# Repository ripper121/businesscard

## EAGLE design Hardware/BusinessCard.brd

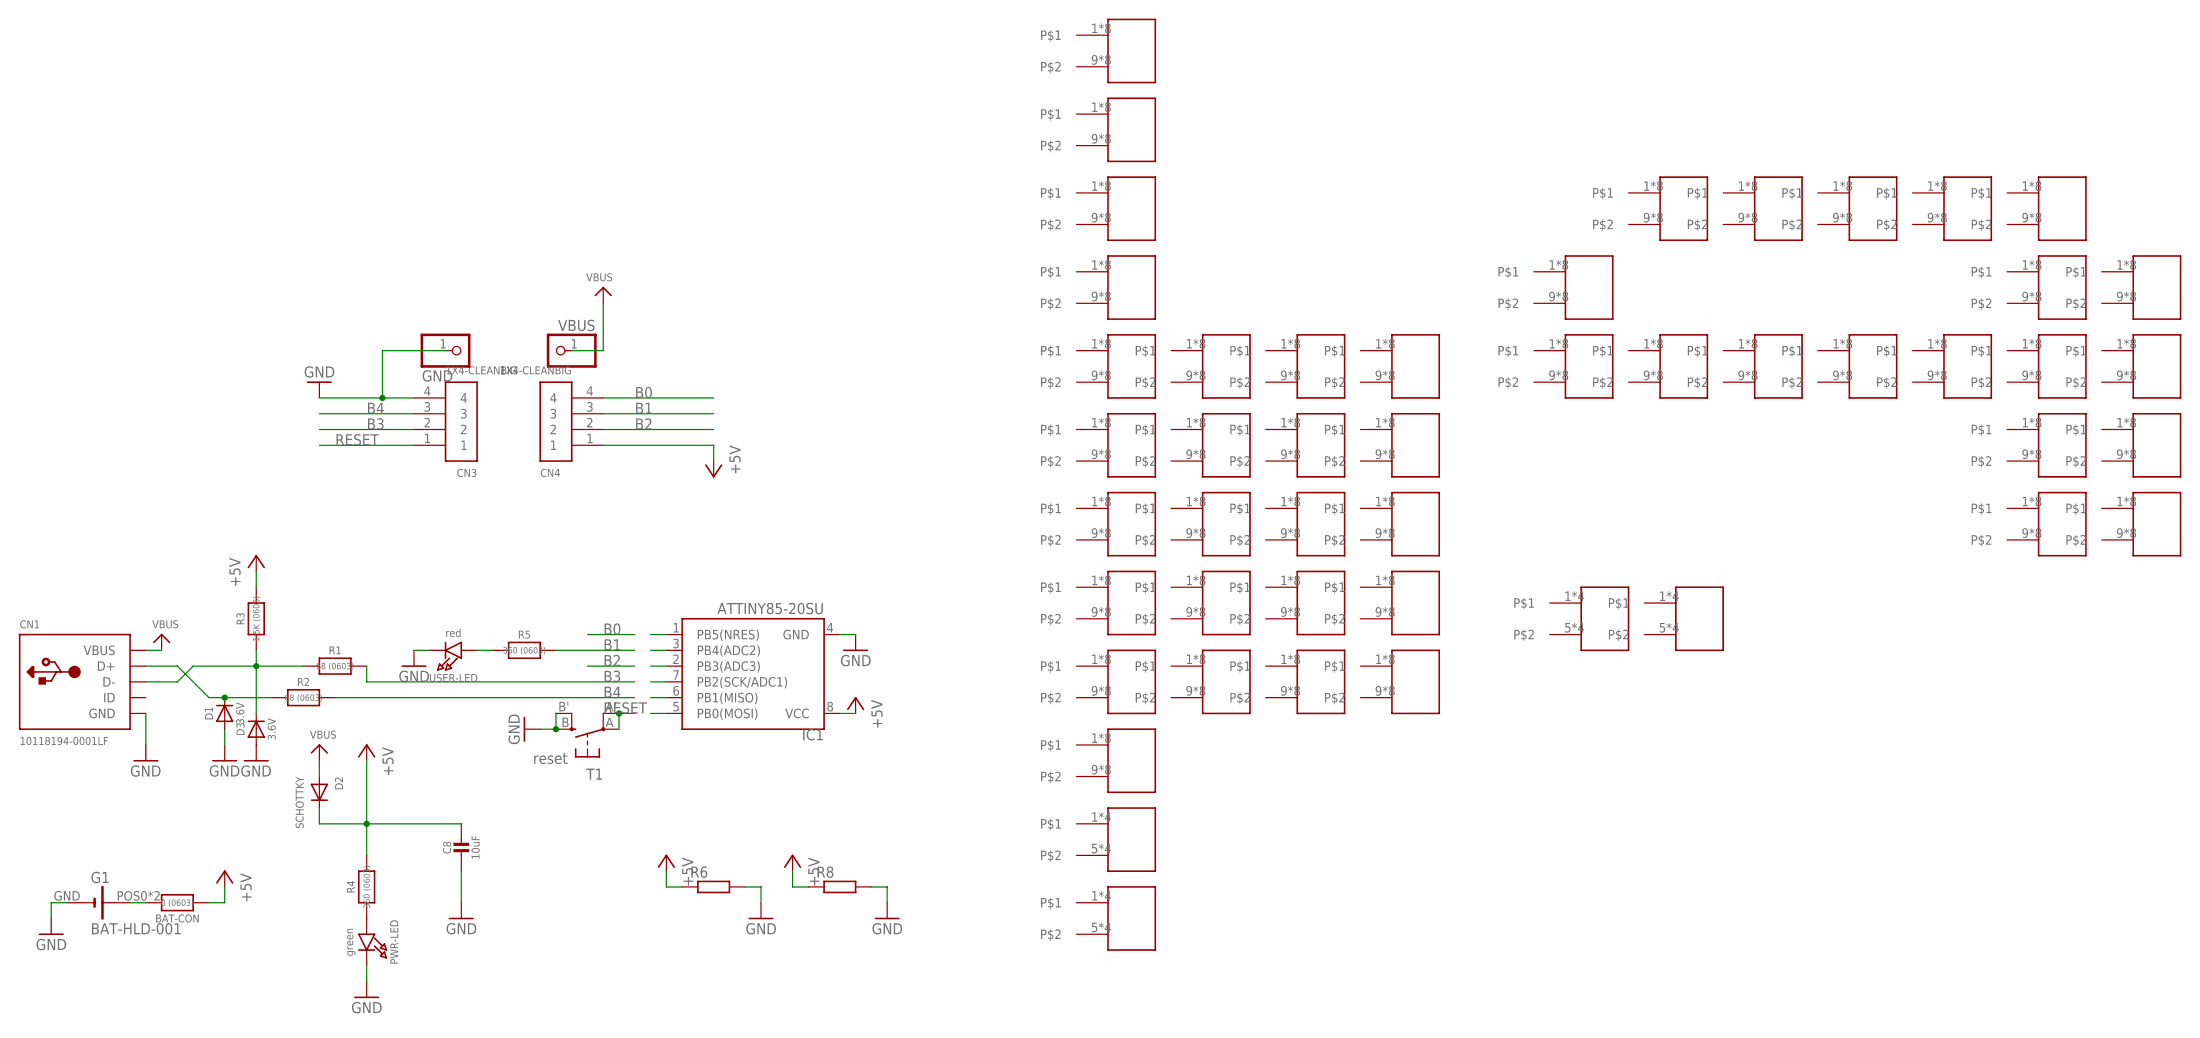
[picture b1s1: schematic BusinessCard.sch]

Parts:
BAT-CON: 0 (0603); 0603-NO
C8: 10uF; 0805-NO
CN1: 10118194-0001LF; 4UCONN_20329
CN3, CN4: 1X4-CLEANBIG; 1X04-CLEANBIG
D1, D3: 3.6V; SOD-323
D2: SCHOTTKY; SOD-123FL
G1: BAT-HLD-001; BK-889
GND: PINHD-1X1CB; 1X01-CLEANBIG
IC1: ATTINY85-20SU; SO08-EIAJ
PWR-LED: green; CHIPLED_0805_NOOUTLINE
R1, R2: 68 (0603); 0603-NO
R3: 1.5K (0603); 0603-NO
R4, R5: 360 (0603); 0603-NO
R6, R8: R-EU_M0805; M0805
T1: reset; EVQ-Q2
U$5, U$6, U$7, U$8, U$9, U$13, U$15, U$17, U$18, U$19, U$20, U$21, U$22, U$23, U$24, U$25, U$26, U$27, U$28, U$29, U$30, U$31, U$32, U$33, U$34, U$35, U$36, U$37, U$40, U$43, U$45, U$48, U$50, U$53, U$55, U$56, U$57, U$58, U$59, U$60, U$61, U$62, U$63, U$64: SMD0805; SMD-0603
U$38, U$39, U$65, U$66: SMD-4
USER-LED: red; CHIPLED_0805_NOOUTLINE
VBUS: PINHD-1X1CB; 1X01-CLEANBIG

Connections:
+5V: BAT-CON.1, C8.1, CN4.1, D2.C, IC1.8 (VCC), R3.2, R4.2, R6.1, R8.1
B0: CN4.4, IC1.5 (PB0(MOSI))
B1: CN4.3, IC1.6 (PB1(MISO)), R5.2
B2: CN4.2, IC1.7 (PB2(SCK/ADC1))
B3: CN3.2, IC1.2 (PB3(ADC3)), R1.2
B4: CN3.3, IC1.3 (PB4(ADC2)), R2.2
GND: C8.2, CN1.BASE@1 (GND), CN1.BASE@2 (GND), CN1.GND, CN1.SPRT@1 (GND), CN1.SPRT@2 (GND), CN1.SPRT@3 (GND), CN1.SPRT@4 (GND), CN3.4, D1.A, D3.A, G1.GND (-), GND.1, IC1.4 (GND), PWR-LED.C, R6.2, R8.2, T1.B (S), T1.B' (S1), USER-LED.C
unnamed: R5.1, USER-LED.A
unnamed: CN1.D+, D1.C, R2.1
unnamed: BAT-CON.2, G1.POS0 (+), G1.POS1 (+)
unnamed: CN1.D-, D3.C, R1.1, R3.1
unnamed: PWR-LED.A, R4.1
RESET: CN3.1, IC1.1 (PB5(NRES)), T1.A, T1.A' (P1)
VBUS: CN1.VBUS, D2.A, VBUS.1

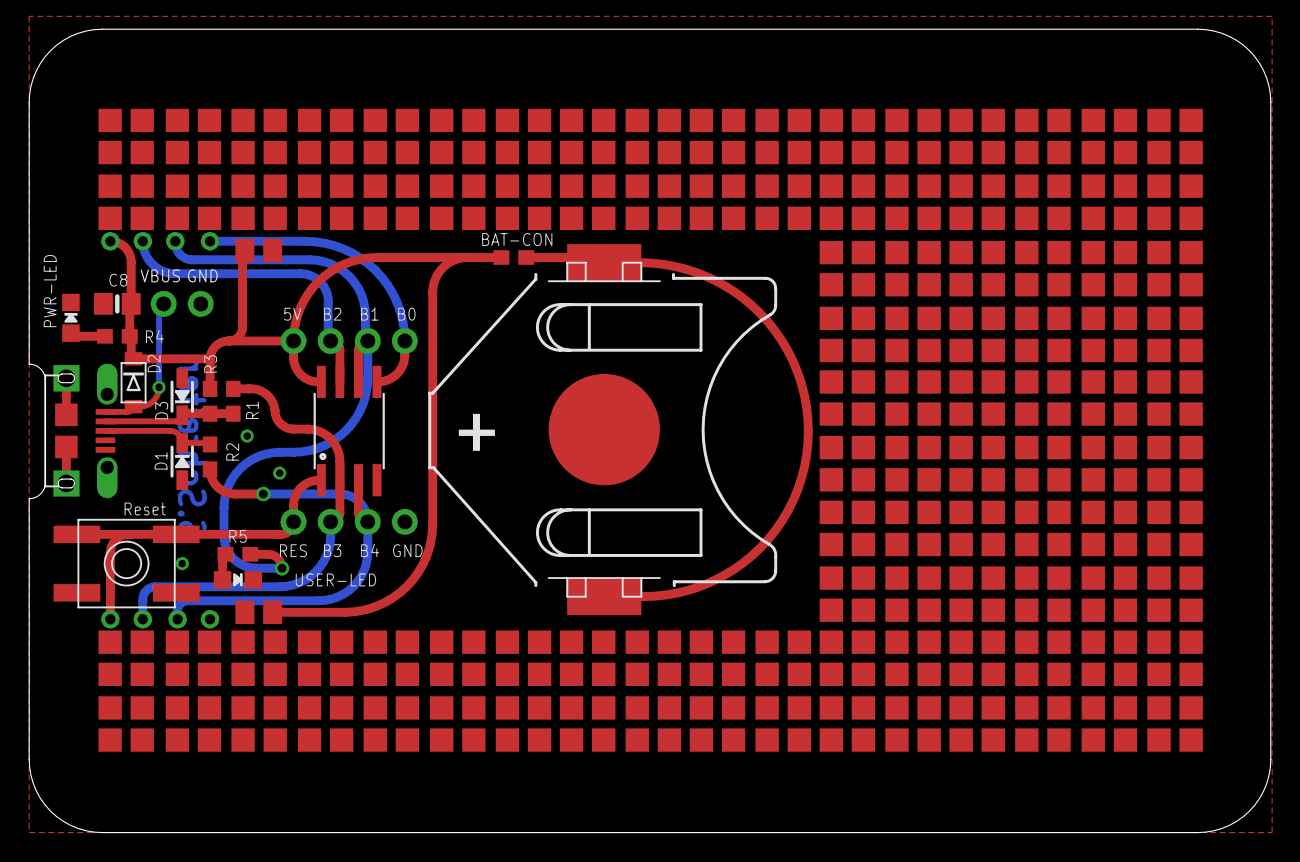
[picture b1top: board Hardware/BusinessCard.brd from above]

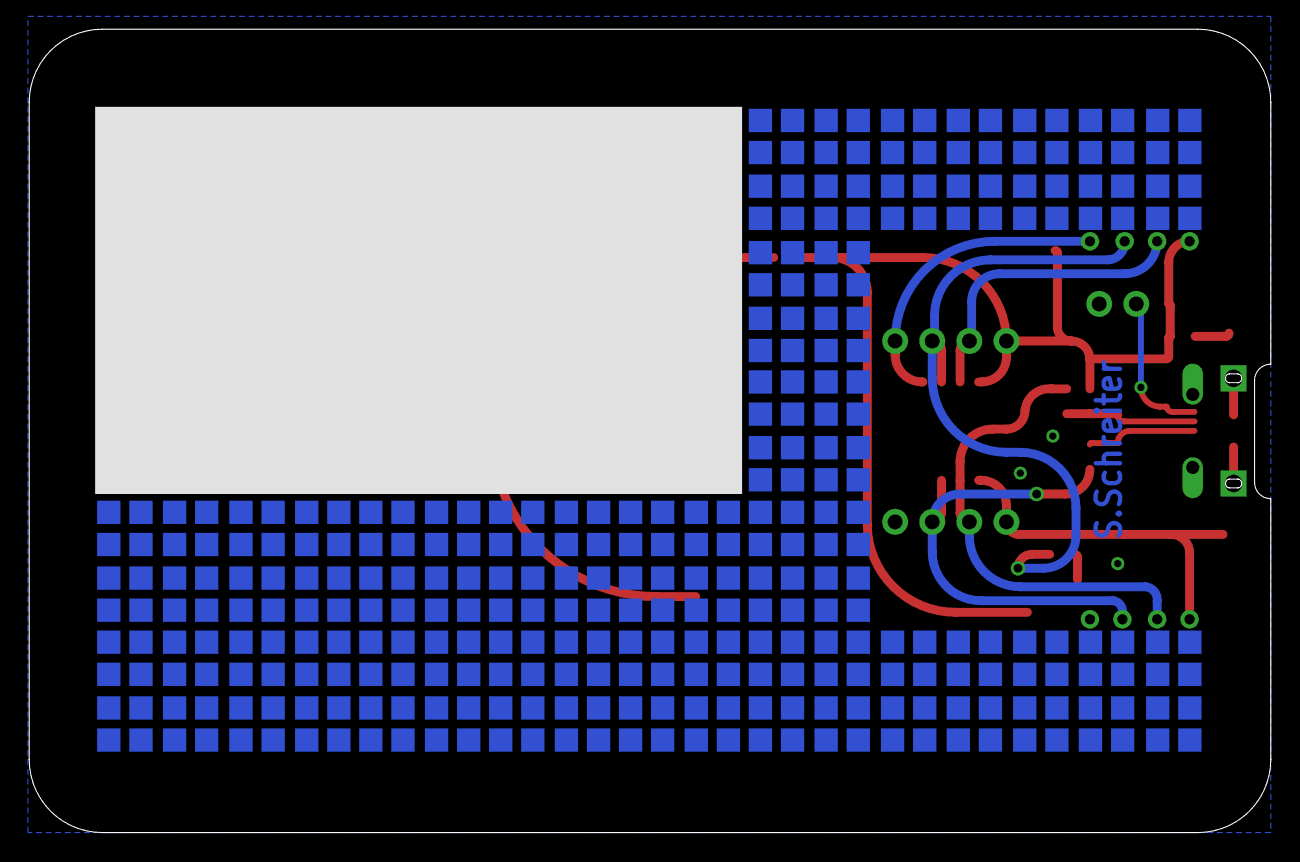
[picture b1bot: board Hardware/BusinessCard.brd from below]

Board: 2 copper layers, 85.0 x 55.0 mm, 70 parts (21 on the bottom side), 14 nets.

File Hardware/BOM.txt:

Stückliste exportiert aus C:/Users/sts/Documents/eagle/BusinessCard/BusinessCard.sch am 04.05.2016 13:13

Qty Value           Device                    Package                Parts                                                                                                                                                                                                                                                             Description                                PROD_ID  VALUE                                                                                                                                                                                                                                                                 RESISTOR, European symbol                                        
1   Tiny85-20-SMT   ATTINY45TINY85-20-SMT     SO08-EIAJ              IC1                                     
1   10118194-0001LF USBMICRO_20329            4UCONN_20329           CN1                                                   
1   BAT-HLD-001     BK-889                    BK-889                 G1
1   SCHOTTKY        DIODE_SOD-123FL           SOD-123FL              D2
2   68 (0603)       RESISTOR_0603_NOOUT       0603-NO                R1, R2
1   green           LED0805_NOOUTLINE         CHIPLED_0805_NOOUTLINE PWR-LED                                                              
1   red             LED0805_NOOUTLINE         CHIPLED_0805_NOOUTLINE USER-LED
2   360 (0603)      RESISTOR_0603_NOOUT       0603-NO                R4, R5
1   1.5K (0603)     RESISTOR_0603_NOOUT       0603-NO                R3
1   0 (0603)        RESISTOR_0603_NOOUT       0603-NO                BAT-CON    
1   10uF            CAP_CERAMIC0805-NOOUTLINE 0805-NO                C8
2   3.6V            DIODESOD-323              SOD-323                D1, D3

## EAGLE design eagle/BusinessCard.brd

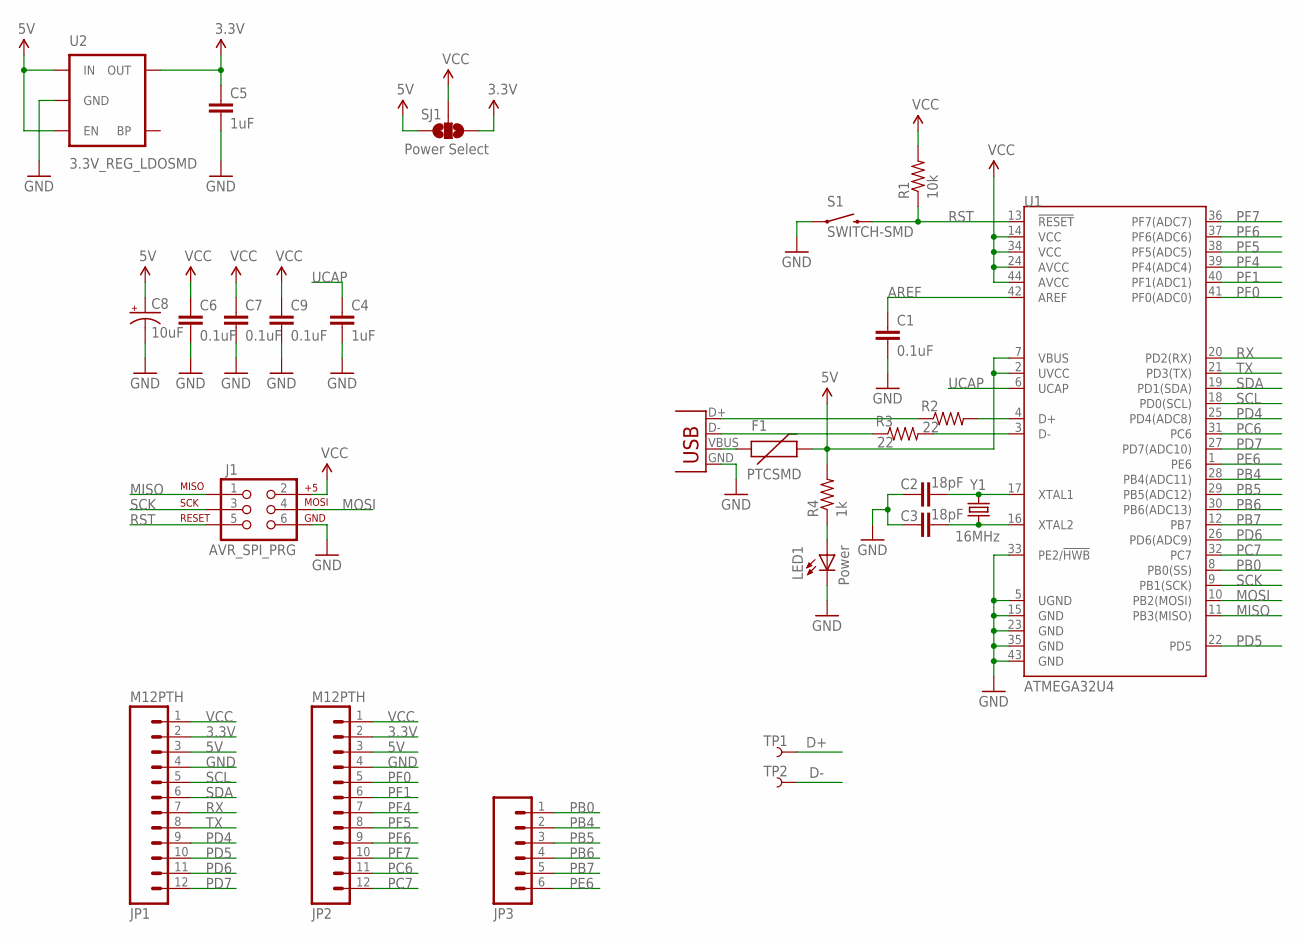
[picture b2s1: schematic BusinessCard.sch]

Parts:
C1, C6, C7, C9: 0.1uF; 0402-CAP
C2, C3: 18pF; 0402-CAP
C4, C5: 1uF; 0402-CAP
C8: 10uF; EIA3216
F1: PTCSMD; PTC-1206
J1: AVR_SPI_PRG; 2X3
JP1, JP2: M12PTH; 1X12
JP3: M06SIP; 1X06
LED1: Power; LED-0603
R1: 10k; 0402-RES
R2, R3: 22; 0402-RES
R4: 1k; 0402-RES
S1: SWITCH-SMD; TACTILE_SWITCH_SMD
SJ1: Power Select; SJ_3_PASTE2&3
TP1, TP2: TEST-POINT3; PAD.03X.03
U1: ATMEGA32U4; QFN-44-NOPAD
U2: 3.3V_REG_LDOSMD; SOT23-5
X1: USBSMD; USB-MINIB
Y1: 16MHz; CRYSTAL-SMD-5X3

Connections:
3.3V: C5.1, JP1.2, JP2.2, SJ1.1, U2.5 (OUT)
5V: C8.A (+), F1.2, JP1.3, JP2.3, R4.2, SJ1.3, U1.2 (UVCC), U1.7 (VBUS), U2.1 (IN), U2.3 (EN)
AREF: C1.1, U1.42 (AREF)
D+: R2.1, TP1.P$1, X1.D+
D-: R3.1, TP2.P$1, X1.D-
GND: C1.2, C2.1, C3.1, C4.2, C5.2, C6.2, C7.2, C8.C (-), C9.2, J1.6, JP1.4, JP2.4, LED1.C, S1.1, U1.5 (UGND), U1.15 (GND), U1.23 (GND), U1.33 (PE2/!HWB), U1.35 (GND), U1.43 (GND), U2.2 (GND), X1.GND
MISO: J1.1, U1.11 (PB3(MISO))
MOSI: J1.4, U1.10 (PB2(MOSI))
unnamed: C2.2, U1.17 (XTAL1), Y1.3 (2)
unnamed: C3.2, U1.16 (XTAL2), Y1.1
unnamed: F1.1, X1.VBUS
unnamed: R2.2, U1.4 (D+)
unnamed: R3.2, U1.3 (D-)
unnamed: LED1.A, R4.1
PB0: JP3.1, U1.8 (PB0(SS))
PB4: JP3.2, U1.28 (PB4(ADC11))
PB5: JP3.3, U1.29 (PB5(ADC12))
PB6: JP3.4, U1.30 (PB6(ADC13))
PB7: JP3.5, U1.12 (PB7)
PC6: JP2.11, U1.31 (PC6)
PC7: JP2.12, U1.32 (PC7)
PD4: JP1.9, U1.25 (PD4(ADC8))
PD5: JP1.10, U1.22 (PD5)
PD6: JP1.11, U1.26 (PD6(ADC9))
PD7: JP1.12, U1.27 (PD7(ADC10))
PE6: JP3.6, U1.1 (PE6)
PF0: JP2.5, U1.41 (PF0(ADC0))
PF1: JP2.6, U1.40 (PF1(ADC1))
PF4: JP2.7, U1.39 (PF4(ADC4))
PF5: JP2.8, U1.38 (PF5(ADC5))
PF6: JP2.9, U1.37 (PF6(ADC6))
PF7: JP2.10, U1.36 (PF7(ADC7))
RST: J1.5, R1.1, S1.3 (2), U1.13 (!RESET)
RX: JP1.7, U1.20 (PD2(RX))
SCK: J1.3, U1.9 (PB1(SCK))
SCL: JP1.5, U1.18 (PD0(SCL))
SDA: JP1.6, U1.19 (PD1(SDA))
TX: JP1.8, U1.21 (PD3(TX))
UCAP: C4.1, U1.6 (UCAP)
VCC: C6.1, C7.1, C9.1, J1.2, JP1.1, JP2.1, R1.2, SJ1.2, U1.14 (VCC), U1.24 (AVCC), U1.34 (VCC), U1.44 (AVCC)

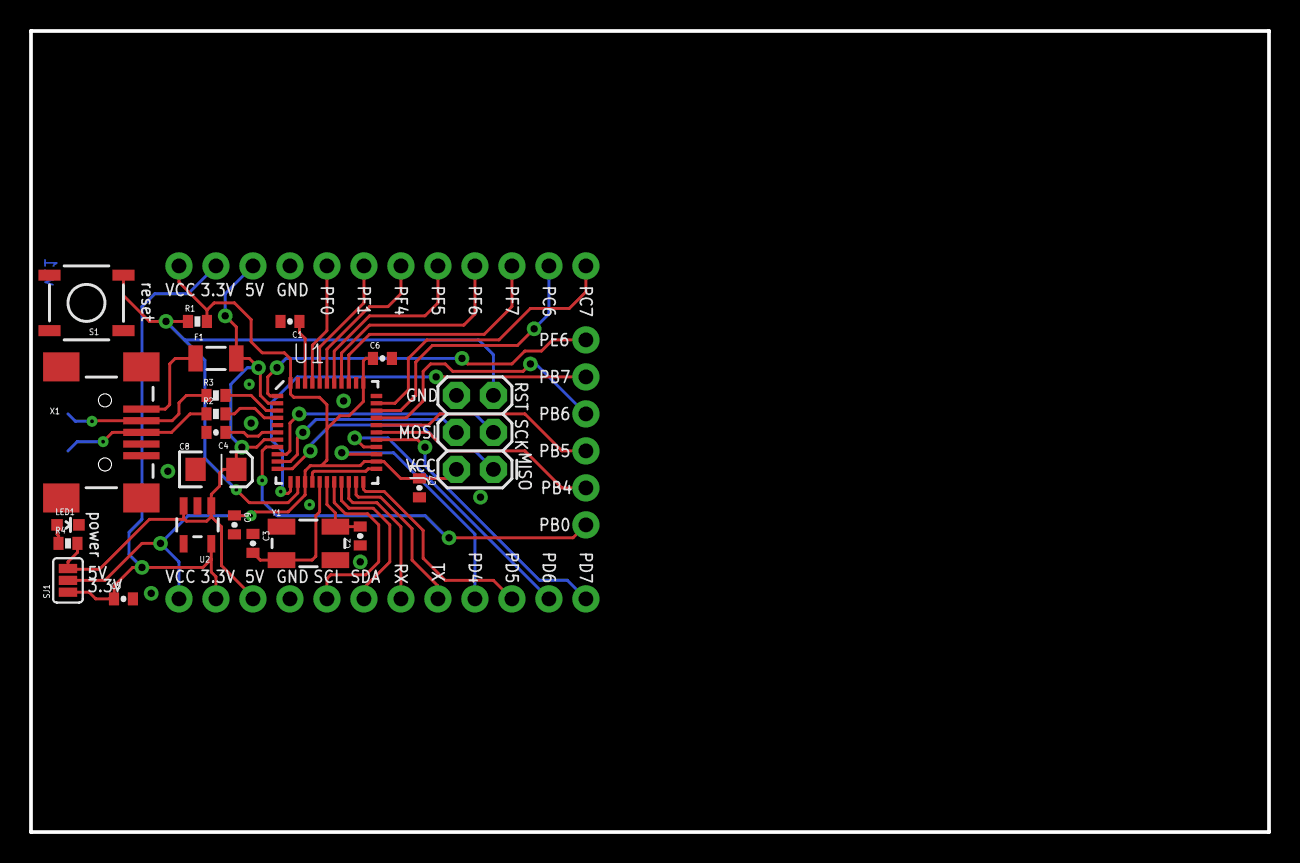
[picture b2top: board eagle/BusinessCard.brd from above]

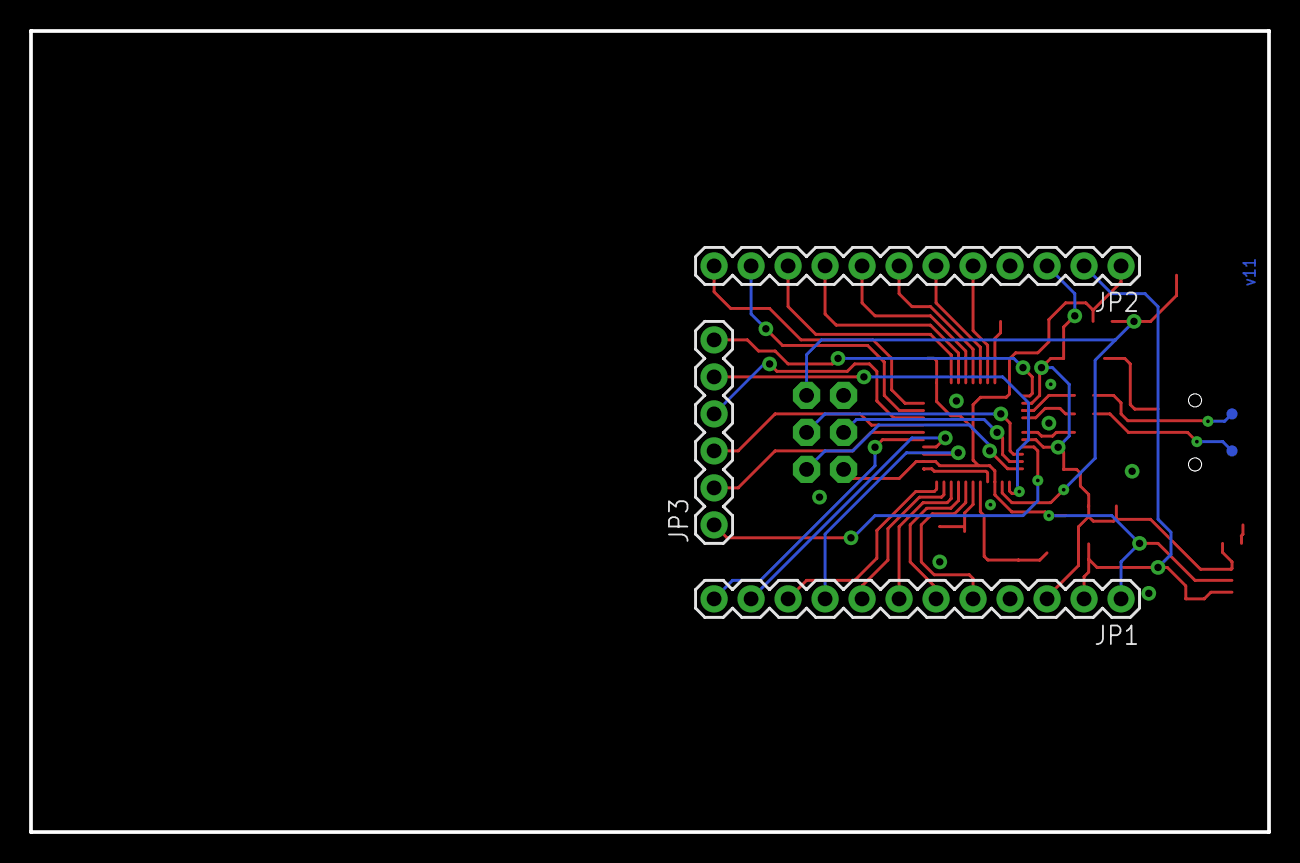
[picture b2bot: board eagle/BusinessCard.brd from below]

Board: 2 copper layers, 85.0 x 55.0 mm, 27 parts (5 on the bottom side), 40 nets.

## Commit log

2016-05-09 Final RC
2016-05-09 Original Hex+Libs

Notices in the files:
parts and their libraries:
microbuilder: This work is placed in the public domain, and may be freely used for commercial and non-commercial work with the following conditions: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
SparkFun-DigitalIC: Licensing: Creative Commons ShareAlike 4.0 International - https://creativecommons.org/licenses/by-sa/4.0
